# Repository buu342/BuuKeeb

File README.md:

# BuuKeeb

I've been wanting a decent mechanical keyboard for a while but I've been having a hard time finding something which fit into all of these categories:
- 100% (105 keys)
- ISO Enter
- [QMK](https://qmk.fm/) support
- LED indicators for Caps Lock, Numlock, and Scroll Lock (This one apparently is really difficult to find despite being standard in keyboards for centuries!)

I saw a Glorious PC GMMK Barebones Keyboard for 30€ which seemed to check all of these boxes (including per-key RGB which is a nice to have), but unfortunately the PCB revision I received had a crappy 8-bit MCU, which meant that writing QMK support for it would be infeasible. The case it came with was mostly metal and pretty nice however, so I decided to make a clone of the PCB, but with an STM32. This would also serve as a cool hardware design learning experience for me!

The BuuKeeb™®© features:
- 105 keys with ISO enter for the 0.01% population of the world who types on a Portuguese layout.
- Hotswappable MX switches.
- N-Key Rollover.
- Per Key LEDs on the north side, individually addressible. [OpenRGB](https://openrgb.org/) support. Key colors savable to persistent storage.
- STM32 MCU for QMK support.
- LED indicators for Caps Lock, Numlock, and Scroll Lock (incredible feature, I know).
- My face on the keyboard for added narcissism.
- Functional. Definitely.

### Keyboard Macros:

* **Alt GR + ESC** - Clear the EEPROM
* **Alt GR + F1** - Decrease the screen brightness
* **Alt GR + F2** - Increase the screen brightness
* **Alt GR + F3** - Projection mode (Windows + P)
* **Alt GR + F4** - Open search bar
* **Alt GR + F5** - Previous track
* **Alt GR + F6** - Pause/Play
* **Alt GR + F7** - Next track
* **Alt GR + F8** - Mute
* **Alt GR + F9** - Decrease volume
* **Alt GR + F10** - Increase volume
* **Alt GR + F11** - Decrease backlight brightness
* **Alt GR + F12** - Increase backlight brightness
* **Alt GR + PrntScr** - Mute microphone
* **Alt GR + ScrLck** - Eject disk
* **Alt GR + Pause** - Suspend/Sleep PC
* **CTRL + Alt GR + ESC** - Save OpenRGB Direct Mode colors to persistent memory

### Editing in KiCad

The design uses [marbastlib](https://github.com/ebastler/marbastlib) for some components so make sure you have that installed before opening the project in KiCad.

### Ordering

The `production` folder provides all the files you need for JLCPCB. You can zip up the entire folder and feed it to JLC. 

During the BOM selection, you can refer to the `bom-JLCPCB Assembly Order.xls` file to look at what components I used when I ordered my PCBs.

### Compiling the QMK Firmware:

1. Download the [OpenRGB QMK Community Module](https://gitlab.com/OpenRGBDevelopers/QMK-OpenRGB) repository.
2. Place it inside the `qmk_firmware/modules` folder and rename it to `openrgb`
3. If your copy of the qmk firmware does not ship with a `buukeeb` folder inside the `qmk_firmware/keyboards` folder, copy the QMK folder from my repository and put it inside the `qmk_firmware/keyboards`, renaming it to `buukeeb` (alternatively place a symbolic link instead).
4. Compile the firmware using your preferred method. I am on Linux so I used `qmk compile -kb buukeeb -km default`.
5. To flash the keyboard, hold down the BOOT button on the back of the board (above the 3 status indicator LEDs) and plug it into the PC. You can then let go of the button and flash it using your preferred method. I am on Linux so I used `qmk flash -kb buukeeb -km default`. 

### Special Thanks:

- [BigBass](https://github.com/bigbass1997) for helping me out with a bunch of KiCad questions and reviewing my PCB designs.
- [Keyboard Atelier Discord community](https://kbatelier.org/) for helping me and doing a keyboard review. Specific shoutouts to Quark, Indeed, Moo, The Great Advisor Xaetral™, Sune, and SenseiZéッ for answering general questions. Another big thanks to cadiremar, galile0, Jubakuba, and SenseiZéッ for the keyboard review.
- [QMK Discord community](https://discord.gg/qmk) for helping me bugfix. Specific shoutout to Drashna Jael're for identifying the LED bug.
- [OpenRGB Discord community](https://discord.gg/AQwjJPY) for answering some OpenRGB questions. Specific shoutout to CalcProgrammer1 for answering my questions.

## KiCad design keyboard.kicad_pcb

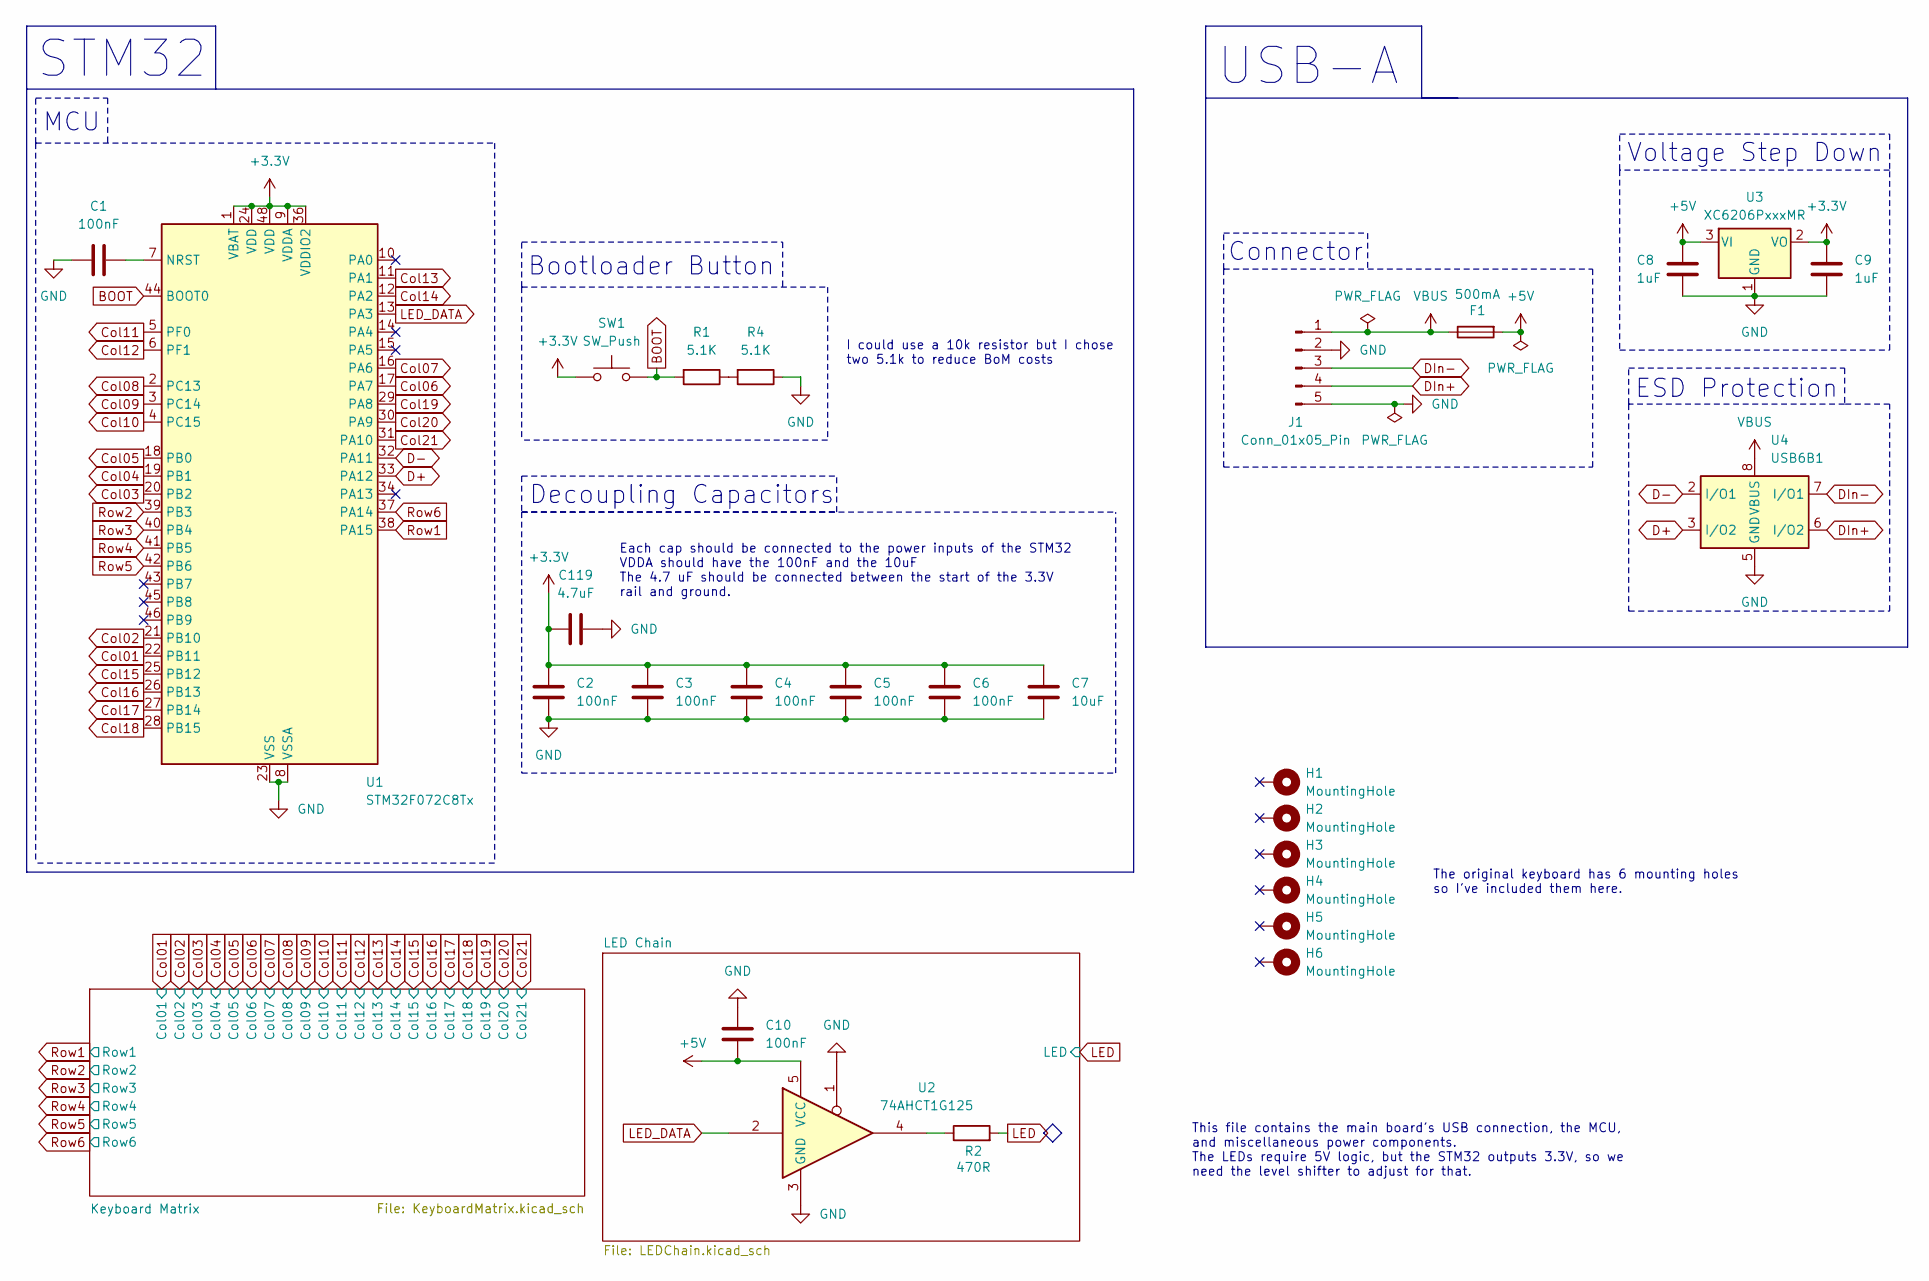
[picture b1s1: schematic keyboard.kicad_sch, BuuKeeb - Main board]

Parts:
C1, C2, C3, C4, C5, C6, C10: 100nF; C_0402_1005Metric
C7: 10uF; C_0603_1608Metric
C8, C9: 1uF; C_0603_1608Metric
C119: 4.7uF; C_0603_1608Metric
F1: 500mA; Fuse_1206_3216Metric
H1, H2, H3, H4, H5, H6: MountingHole; MountingHole_3.5mm_Pad_5.5mm
J1: Conn_01x05_Pin; PinHeader_1x05_P2.00mm_Horizontal
R1, R4: 5.1K; R_0402_1005Metric
R2: 470R; R_0402_1005Metric
SW1: SW_Push; SW_SPST_TL3342
U1: STM32F072C8Tx; LQFP-48_7x7mm_P0.5mm
U2: 74AHCT1G125; TSOP-5_1.65x3.05mm_P0.95mm
U3: XC6206PxxxMR; SOT-23-3
U4: USB6B1; SOIC-8_3.9x4.9mm_P1.27mm

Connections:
+3.3V: C2.1, C3.1, C4.1, C5.1, C6.1, C7.1, C9.1, C119.1, SW1.1, U1.1 (VBAT), U1.9 (VDDA), U1.24 (VDD), U1.36 (VDDIO2), U1.48 (VDD), U3.2 (VO)
+5V: C8.1, C10.2, F1.2, U2.5 (VCC), U3.3 (VI); also elsewhere on the board
BOOT: R1.2, SW1.2, U1.44 (BOOT0)
Col01: U1.22 (PB11); also elsewhere on the board
Col02: U1.21 (PB10); also elsewhere on the board
Col03: U1.20 (PB2); also elsewhere on the board
Col04: U1.19 (PB1); also elsewhere on the board
Col05: U1.18 (PB0); also elsewhere on the board
Col06: U1.17 (PA7); also elsewhere on the board
Col07: U1.16 (PA6); also elsewhere on the board
Col08: U1.2 (PC13); also elsewhere on the board
Col09: U1.3 (PC14); also elsewhere on the board
Col10: U1.4 (PC15); also elsewhere on the board
Col11: U1.5 (PF0); also elsewhere on the board
Col12: U1.6 (PF1); also elsewhere on the board
Col13: U1.11 (PA1); also elsewhere on the board
Col14: U1.12 (PA2); also elsewhere on the board
Col15: U1.25 (PB12); also elsewhere on the board
Col16: U1.26 (PB13); also elsewhere on the board
Col17: U1.27 (PB14); also elsewhere on the board
Col18: U1.28 (PB15); also elsewhere on the board
Col19: U1.29 (PA8); also elsewhere on the board
Col20: U1.30 (PA9); also elsewhere on the board
Col21: U1.31 (PA10); also elsewhere on the board
D+: U1.33 (PA12), U4.3 (I/O2)
D-: U1.32 (PA11), U4.2 (I/O1)
DIn+: J1.4, U4.6 (I/O2)
DIn-: J1.3, U4.7 (I/O1)
GND: C1.2, C2.2, C3.2, C4.2, C5.2, C6.2, C7.2, C8.2, C9.2, C10.1, C119.2, J1.2, J1.5, R4.1, U1.8 (VSSA), U1.23 (VSS), U1.35 (VSS), U1.47 (VSS), U2.1, U2.3 (GND), U3.1 (GND), U4.4 (GND), U4.5 (GND); also elsewhere on the board
LED: R2.2; also elsewhere on the board
LED_DATA: U1.13 (PA3), U2.2
unnamed: R1.1, R4.2
unnamed: R2.1, U2.4
unnamed: C1.1, U1.7 (NRST)
Row1: U1.38 (PA15); also elsewhere on the board
Row2: U1.39 (PB3); also elsewhere on the board
Row3: U1.40 (PB4); also elsewhere on the board
Row4: U1.41 (PB5); also elsewhere on the board
Row5: U1.42 (PB6); also elsewhere on the board
Row6: U1.37 (PA14); also elsewhere on the board
VBUS: F1.1, J1.1, U4.1 (VBUS), U4.8 (VBUS)

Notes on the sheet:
Connector
Voltage Step Down
MCU
The original keyboard has 6 mounting holes so I've included them here.
STM32
ESD Protection
Decoupling Capacitors
This file contains the main board's USB connection, the MCU, and miscellaneous power components. The LEDs require 5V logic, but the STM32 outputs 3.3V, so we need the level shifter to adjust for that.
I could use a 10k resistor but I chose two 5.1k to reduce BoM costs
USB-A
Bootloader Button
Each cap should be connected to the power inputs of the STM32 VDDA should have the 100nF and the 10uF The 4.7 uF should be connected between the start of the 3.3V rail and ground.

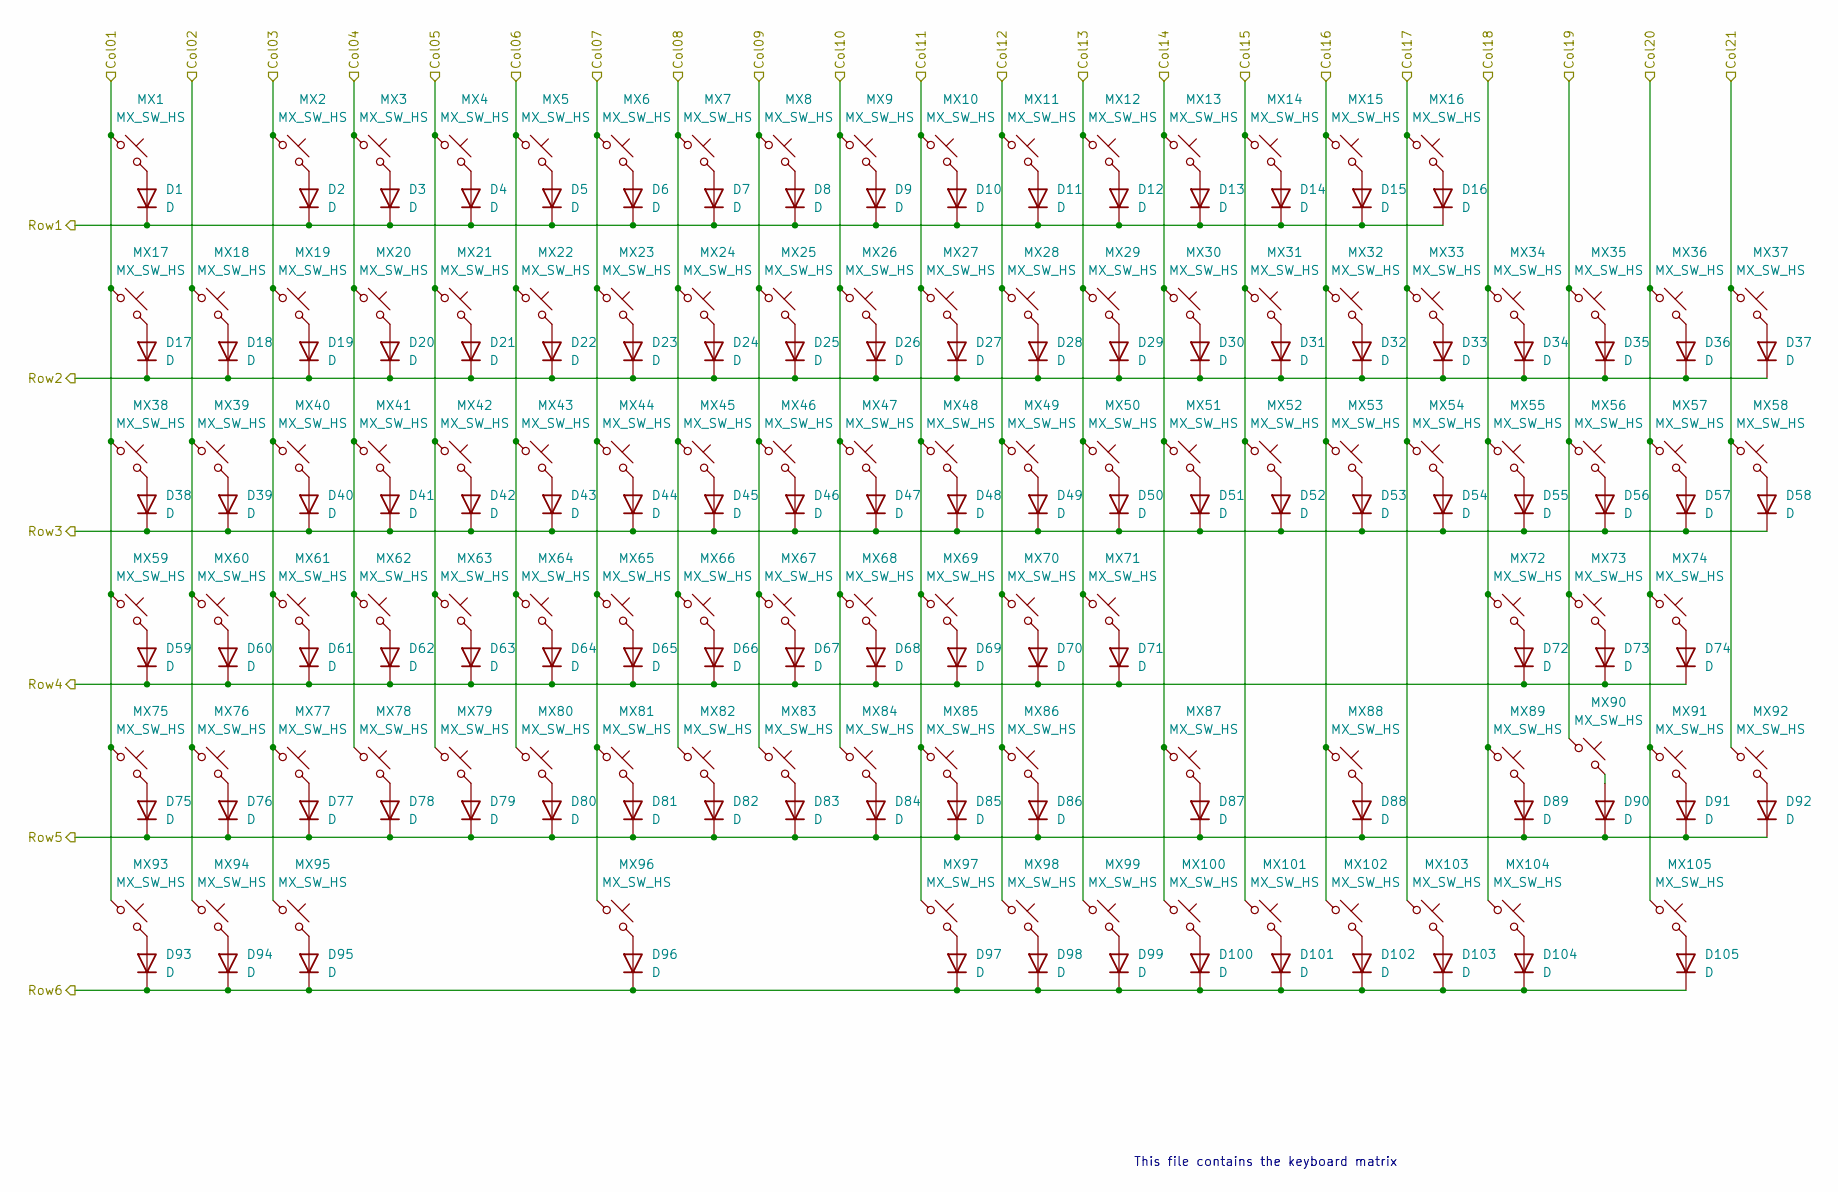
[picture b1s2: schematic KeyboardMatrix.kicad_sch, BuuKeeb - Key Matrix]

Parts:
D1, D2, D3, D4, D5, D6, D7, D8, D9, D10, D11, D12, D13, D14, D15, D16, D17, D18, D19, D20, D21, D22, D23, D24, D25, D26, D27, D28, D29, D30, D31, D32, D33, D34, D35, D36, D37, D38, D39, D40, D41, D42, D43, D44, D45, D46, D47, D48, D49, D50, D51, D52, D53, D54, D55, D56, D57, D58, D59, D60, D61, D62, D63, D64, D65, D66, D67, D68, D69, D70, D71, D72, D73, D74, D75, D76, D77, D78, D79, D80, D81, D82, D83, D84, D85, D86, D87, D88, D89, D90, D91, D92, D93, D94, D95, D96, D97, D98, D99, D100, D101, D102, D103, D104, D105: D; D_SOD-123
MX1, MX2, MX3, MX4, MX5, MX6, MX7, MX8, MX9, MX10, MX11, MX12, MX13, MX14, MX15, MX16, MX17, MX18, MX19, MX20, MX21, MX22, MX23, MX24, MX25, MX26, MX27, MX28, MX29, MX30, MX31, MX32, MX33, MX34, MX35, MX36, MX37, MX38, MX39, MX40, MX41, MX42, MX43, MX44, MX45, MX46, MX47, MX48, MX49, MX50, MX51, MX52, MX53, MX54, MX55, MX56, MX57, MX58, MX59, MX60, MX61, MX62, MX63, MX64, MX65, MX66, MX67, MX68, MX69, MX70, MX71, MX72, MX73, MX74, MX75, MX76, MX77, MX78, MX79, MX80, MX81, MX82, MX83, MX84, MX85, MX86, MX87, MX88, MX89, MX90, MX91, MX92, MX93, MX94, MX95, MX96, MX97, MX98, MX99, MX100, MX101, MX102, MX103, MX104, MX105: MX_SW_HS; SW_MX_HS_CPG151101S11_1.5u_NoHoles

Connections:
Col01: MX1.1, MX17.1, MX38.1, MX59.1, MX75.1, MX93.1; also elsewhere on the board
Col02: MX18.1, MX39.1, MX60.1, MX76.1, MX94.1; also elsewhere on the board
Col03: MX2.1, MX19.1, MX40.1, MX61.1, MX77.1, MX95.1; also elsewhere on the board
Col04: MX3.1, MX20.1, MX41.1, MX62.1, MX78.1; also elsewhere on the board
Col05: MX4.1, MX21.1, MX42.1, MX63.1, MX79.1; also elsewhere on the board
Col06: MX5.1, MX22.1, MX43.1, MX64.1, MX80.1; also elsewhere on the board
Col07: MX6.1, MX23.1, MX44.1, MX65.1, MX81.1, MX96.1; also elsewhere on the board
Col08: MX7.1, MX24.1, MX45.1, MX66.1, MX82.1; also elsewhere on the board
Col09: MX8.1, MX25.1, MX46.1, MX67.1, MX83.1; also elsewhere on the board
Col10: MX9.1, MX26.1, MX47.1, MX68.1, MX84.1; also elsewhere on the board
Col11: MX10.1, MX27.1, MX48.1, MX69.1, MX85.1, MX97.1; also elsewhere on the board
Col12: MX11.1, MX28.1, MX49.1, MX70.1, MX86.1, MX98.1; also elsewhere on the board
Col13: MX12.1, MX29.1, MX50.1, MX71.1, MX99.1; also elsewhere on the board
Col14: MX13.1, MX30.1, MX51.1, MX87.1, MX100.1; also elsewhere on the board
Col15: MX14.1, MX31.1, MX52.1, MX101.1; also elsewhere on the board
Col16: MX15.1, MX32.1, MX53.1, MX88.1, MX102.1; also elsewhere on the board
Col17: MX16.1, MX33.1, MX54.1, MX103.1; also elsewhere on the board
Col18: MX34.1, MX55.1, MX72.1, MX89.1, MX104.1; also elsewhere on the board
Col19: MX35.1, MX56.1, MX73.1, MX90.1; also elsewhere on the board
Col20: MX36.1, MX57.1, MX74.1, MX91.1, MX105.1; also elsewhere on the board
Col21: MX37.1, MX58.1, MX92.1; also elsewhere on the board
unnamed: D1.2 (A), MX1.2
unnamed: D2.2 (A), MX2.2
unnamed: D3.2 (A), MX3.2
unnamed: D4.2 (A), MX4.2
unnamed: D5.2 (A), MX5.2
unnamed: D6.2 (A), MX6.2
unnamed: D7.2 (A), MX7.2
unnamed: D8.2 (A), MX8.2
unnamed: D9.2 (A), MX9.2
unnamed: D10.2 (A), MX10.2
unnamed: D11.2 (A), MX11.2
unnamed: D12.2 (A), MX12.2
unnamed: D13.2 (A), MX13.2
unnamed: D14.2 (A), MX14.2
unnamed: D15.2 (A), MX15.2
unnamed: D16.2 (A), MX16.2
unnamed: D17.2 (A), MX17.2
unnamed: D18.2 (A), MX18.2
unnamed: D19.2 (A), MX19.2
unnamed: D20.2 (A), MX20.2
unnamed: D21.2 (A), MX21.2
unnamed: D22.2 (A), MX22.2
unnamed: D23.2 (A), MX23.2
unnamed: D24.2 (A), MX24.2
unnamed: D25.2 (A), MX25.2
unnamed: D26.2 (A), MX26.2
unnamed: D27.2 (A), MX27.2
unnamed: D28.2 (A), MX28.2
unnamed: D29.2 (A), MX29.2
unnamed: D30.2 (A), MX30.2
unnamed: D31.2 (A), MX31.2
unnamed: D32.2 (A), MX32.2
unnamed: D33.2 (A), MX33.2
unnamed: D34.2 (A), MX34.2
unnamed: D35.2 (A), MX35.2
unnamed: D36.2 (A), MX36.2
unnamed: D37.2 (A), MX37.2
unnamed: D38.2 (A), MX38.2
unnamed: D39.2 (A), MX39.2
unnamed: D40.2 (A), MX40.2
unnamed: D41.2 (A), MX41.2
unnamed: D42.2 (A), MX42.2
unnamed: D43.2 (A), MX43.2
unnamed: D44.2 (A), MX44.2
unnamed: D45.2 (A), MX45.2
unnamed: D46.2 (A), MX46.2
unnamed: D47.2 (A), MX47.2
unnamed: D48.2 (A), MX48.2
unnamed: D49.2 (A), MX49.2
unnamed: D50.2 (A), MX50.2
unnamed: D51.2 (A), MX51.2
unnamed: D52.2 (A), MX52.2
unnamed: D53.2 (A), MX53.2
unnamed: D54.2 (A), MX54.2
unnamed: D55.2 (A), MX55.2
unnamed: D56.2 (A), MX56.2
unnamed: D57.2 (A), MX57.2
unnamed: D58.2 (A), MX58.2
unnamed: D59.2 (A), MX59.2
unnamed: D60.2 (A), MX60.2
unnamed: D61.2 (A), MX61.2
unnamed: D62.2 (A), MX62.2
unnamed: D63.2 (A), MX63.2
unnamed: D64.2 (A), MX64.2
unnamed: D65.2 (A), MX65.2
unnamed: D66.2 (A), MX66.2
unnamed: D67.2 (A), MX67.2
unnamed: D68.2 (A), MX68.2
unnamed: D69.2 (A), MX69.2
unnamed: D70.2 (A), MX70.2
unnamed: D71.2 (A), MX71.2
unnamed: D72.2 (A), MX72.2
unnamed: D73.2 (A), MX73.2
unnamed: D74.2 (A), MX74.2
unnamed: D75.2 (A), MX75.2
unnamed: D76.2 (A), MX76.2
unnamed: D77.2 (A), MX77.2
unnamed: D78.2 (A), MX78.2
unnamed: D79.2 (A), MX79.2
unnamed: D80.2 (A), MX80.2
unnamed: D81.2 (A), MX81.2
unnamed: D82.2 (A), MX82.2
unnamed: D83.2 (A), MX83.2
unnamed: D84.2 (A), MX84.2
unnamed: D85.2 (A), MX85.2
unnamed: D86.2 (A), MX86.2
unnamed: D87.2 (A), MX87.2
unnamed: D88.2 (A), MX88.2
unnamed: D89.2 (A), MX89.2
unnamed: D90.2 (A), MX90.2
unnamed: D91.2 (A), MX91.2
unnamed: D92.2 (A), MX92.2
unnamed: D93.2 (A), MX93.2
unnamed: D94.2 (A), MX94.2
unnamed: D95.2 (A), MX95.2
unnamed: D96.2 (A), MX96.2
unnamed: D97.2 (A), MX97.2
unnamed: D98.2 (A), MX98.2
unnamed: D99.2 (A), MX99.2
unnamed: D100.2 (A), MX100.2
unnamed: D101.2 (A), MX101.2
unnamed: D102.2 (A), MX102.2
unnamed: D103.2 (A), MX103.2
unnamed: D104.2 (A), MX104.2
unnamed: D105.2 (A), MX105.2
Row1: D1.1 (K), D2.1 (K), D3.1 (K), D4.1 (K), D5.1 (K), D6.1 (K), D7.1 (K), D8.1 (K), D9.1 (K), D10.1 (K), D11.1 (K), D12.1 (K), D13.1 (K), D14.1 (K), D15.1 (K), D16.1 (K); also elsewhere on the board
Row2: D17.1 (K), D18.1 (K), D19.1 (K), D20.1 (K), D21.1 (K), D22.1 (K), D23.1 (K), D24.1 (K), D25.1 (K), D26.1 (K), D27.1 (K), D28.1 (K), D29.1 (K), D30.1 (K), D31.1 (K), D32.1 (K), D33.1 (K), D34.1 (K), D35.1 (K), D36.1 (K), D37.1 (K); also elsewhere on the board
Row3: D38.1 (K), D39.1 (K), D40.1 (K), D41.1 (K), D42.1 (K), D43.1 (K), D44.1 (K), D45.1 (K), D46.1 (K), D47.1 (K), D48.1 (K), D49.1 (K), D50.1 (K), D51.1 (K), D52.1 (K), D53.1 (K), D54.1 (K), D55.1 (K), D56.1 (K), D57.1 (K), D58.1 (K); also elsewhere on the board
Row4: D59.1 (K), D60.1 (K), D61.1 (K), D62.1 (K), D63.1 (K), D64.1 (K), D65.1 (K), D66.1 (K), D67.1 (K), D68.1 (K), D69.1 (K), D70.1 (K), D71.1 (K), D72.1 (K), D73.1 (K), D74.1 (K); also elsewhere on the board
Row5: D75.1 (K), D76.1 (K), D77.1 (K), D78.1 (K), D79.1 (K), D80.1 (K), D81.1 (K), D82.1 (K), D83.1 (K), D84.1 (K), D85.1 (K), D86.1 (K), D87.1 (K), D88.1 (K), D89.1 (K), D90.1 (K), D91.1 (K), D92.1 (K); also elsewhere on the board
Row6: D93.1 (K), D94.1 (K), D95.1 (K), D96.1 (K), D97.1 (K), D98.1 (K), D99.1 (K), D100.1 (K), D101.1 (K), D102.1 (K), D103.1 (K), D104.1 (K), D105.1 (K); also elsewhere on the board

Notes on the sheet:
This file contains the keyboard matrix

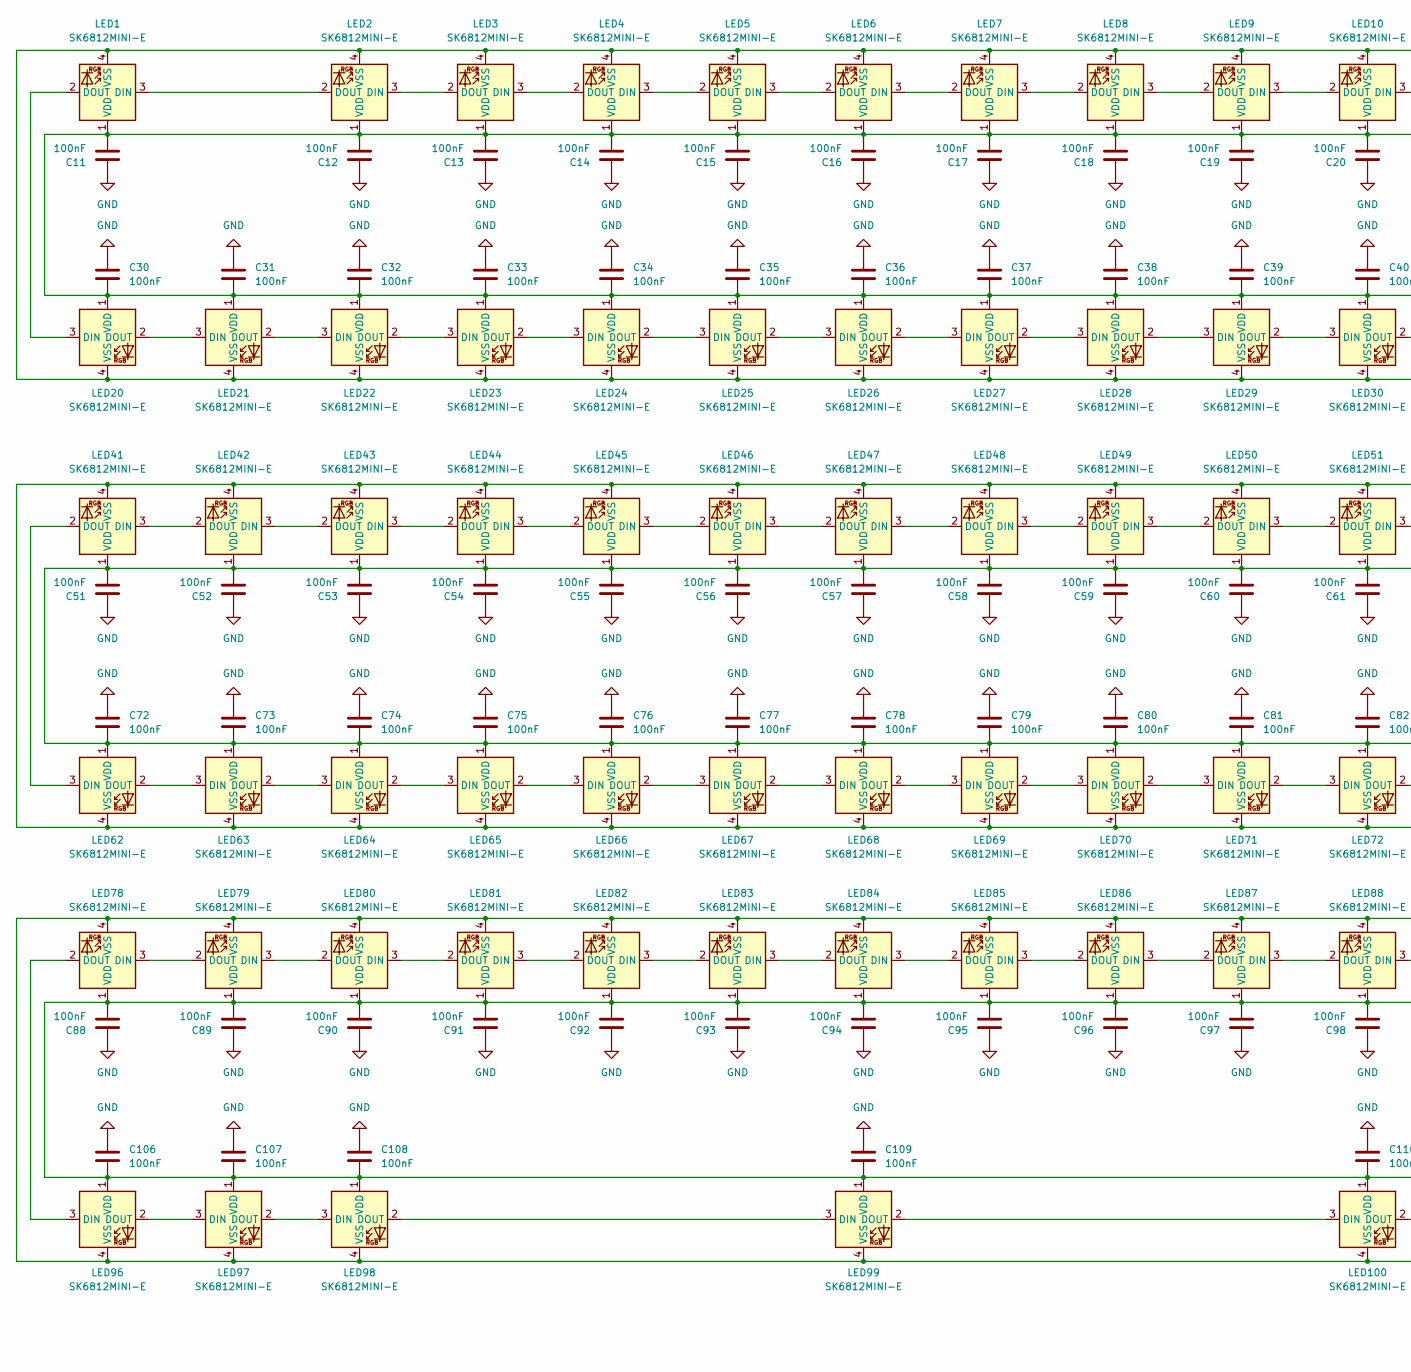
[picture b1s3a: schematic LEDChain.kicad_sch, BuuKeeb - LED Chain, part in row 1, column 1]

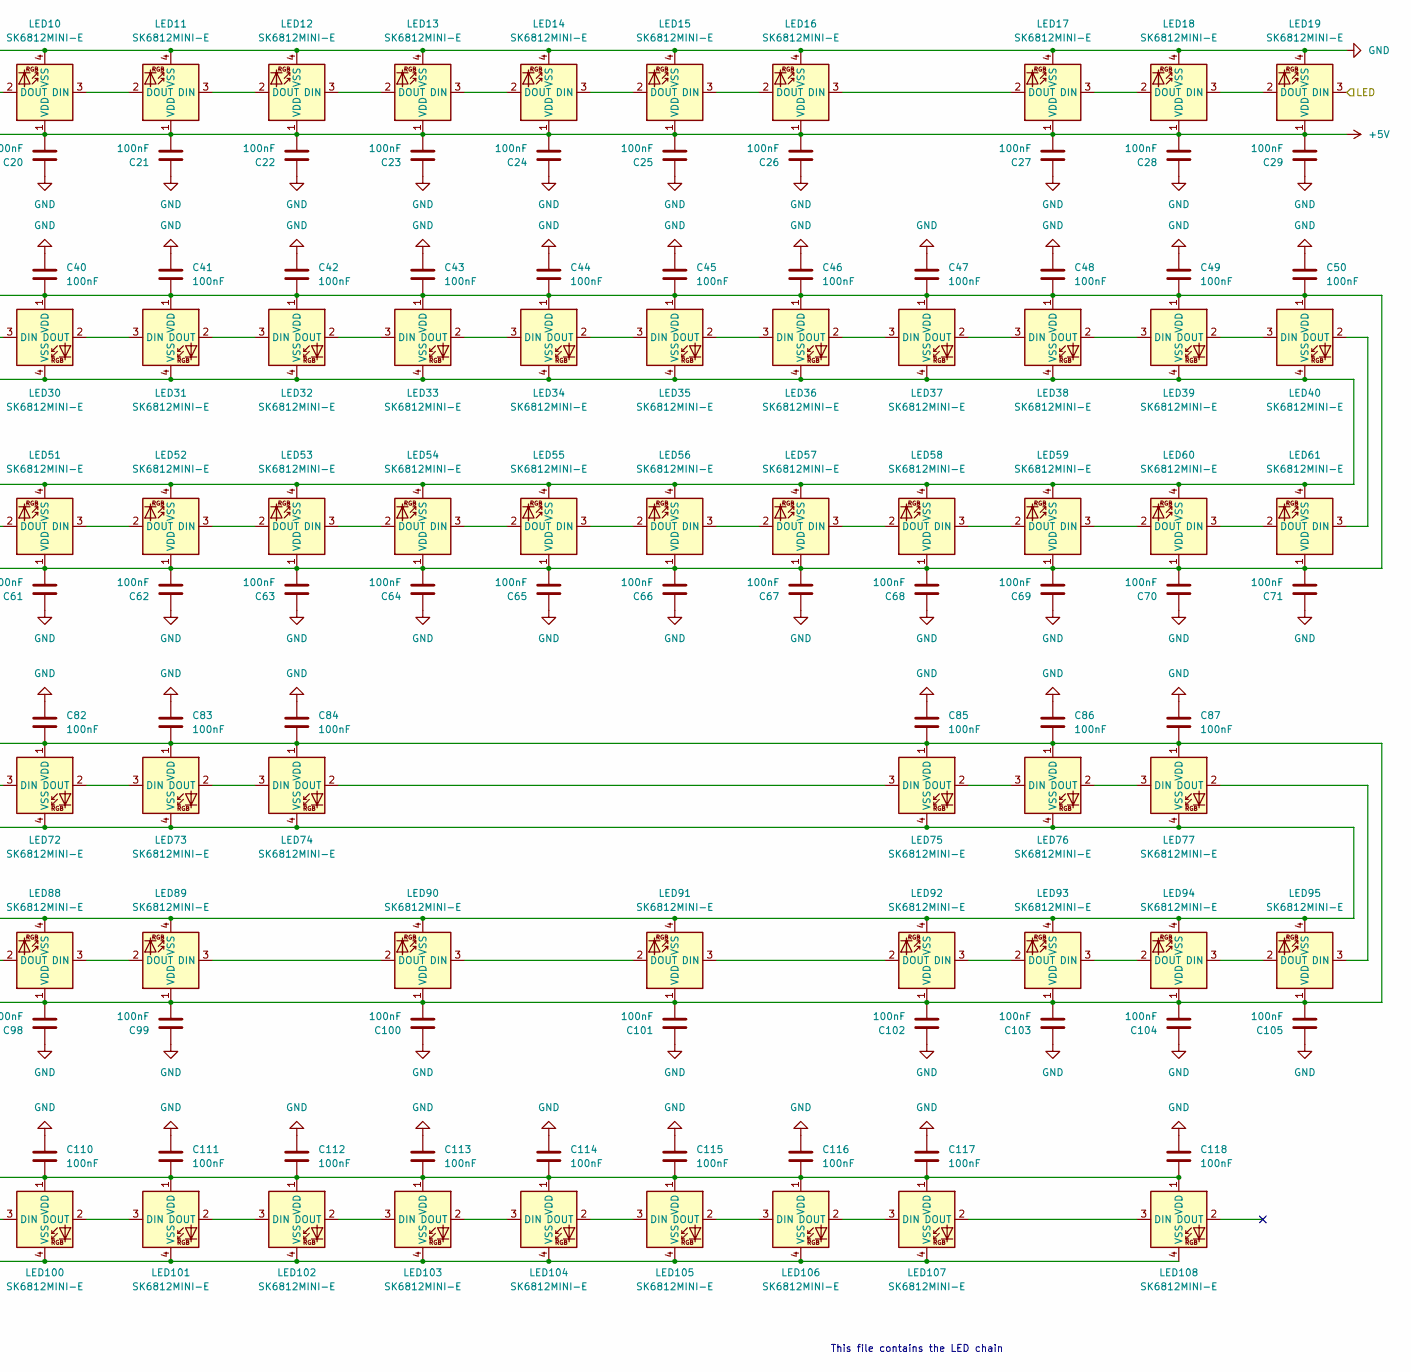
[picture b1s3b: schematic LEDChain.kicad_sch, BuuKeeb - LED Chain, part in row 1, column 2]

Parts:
C11, C12, C13, C14, C15, C16, C17, C18, C19, C20, C21, C22, C23, C24, C25, C26, C27, C28, C29, C30, C31, C32, C33, C34, C35, C36, C37, C38, C39, C40, C41, C42, C43, C44, C45, C46, C47, C48, C49, C50, C51, C52, C53, C54, C55, C56, C57, C58, C59, C60, C61, C62, C63, C64, C65, C66, C67, C68, C69, C70, C71, C72, C73, C74, C75, C76, C77, C78, C79, C80, C81, C82, C83, C84, C85, C86, C87, C88, C89, C90, C91, C92, C93, C94, C95, C96, C97, C98, C99, C100, C101, C102, C103, C104, C105, C106, C107, C108, C109, C110, C111, C112, C113, C114, C115, C116, C117, C118: 100nF; C_0402_1005Metric
LED1, LED2, LED3, LED4, LED5, LED6, LED7, LED8, LED9, LED10, LED11, LED12, LED13, LED14, LED15, LED16, LED17, LED18, LED19, LED20, LED21, LED22, LED23, LED24, LED25, LED26, LED27, LED28, LED29, LED30, LED31, LED32, LED33, LED34, LED35, LED36, LED37, LED38, LED39, LED40, LED41, LED42, LED43, LED44, LED45, LED46, LED47, LED48, LED49, LED50, LED51, LED52, LED53, LED54, LED55, LED56, LED57, LED58, LED59, LED60, LED61, LED62, LED63, LED64, LED65, LED66, LED67, LED68, LED69, LED70, LED71, LED72, LED73, LED74, LED75, LED76, LED77, LED78, LED79, LED80, LED81, LED82, LED83, LED84, LED85, LED86, LED87, LED88, LED89, LED90, LED91, LED92, LED93, LED94, LED95, LED96, LED97, LED98, LED99, LED100, LED101, LED102, LED103, LED104, LED105, LED106, LED107, LED108: SK6812MINI-E; LED_6028R_NoHoles

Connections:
+5V: C11.2, C12.2, C13.2, C14.2, C15.2, C16.2, C17.2, C18.2, C19.2, C20.2, C21.2, C22.2, C23.2, C24.2, C25.2, C26.2, C27.2, C28.2, C29.1, C30.2, C31.2, C32.2, C33.2, C34.2, C35.2, C36.2, C37.2, C38.2, C39.2, C40.2, C41.2, C42.2, C43.2, C44.2, C45.2, C46.2, C47.2, C48.2, C49.2, C50.2, C51.2, C52.2, C53.2, C54.2, C55.2, C56.2, C57.2, C58.2, C59.2, C60.2, C61.2, C62.2, C63.2, C64.2, C65.2, C66.2, C67.2, C68.2, C69.2, C70.2, C71.2, C72.2, C73.2, C74.2, C75.2, C76.2, C77.2, C78.2, C79.2, C80.2, C81.2, C82.2, C83.2, C84.2, C85.2, C86.2, C87.2, C88.2, C89.2, C90.2, C91.2, C92.2, C93.2, C94.2, C95.2, C96.2, C97.2, C98.2, C99.2, C100.2, C101.2, C102.2, C103.2, C104.2, C105.2, C106.2, C107.2, C108.2, C109.2, C110.2, C111.2, C112.2, C113.2, C114.2, C115.2, C116.2, C117.2, C118.2, LED1.1 (VDD), LED2.1 (VDD), LED3.1 (VDD), LED4.1 (VDD), LED5.1 (VDD), LED6.1 (VDD), LED7.1 (VDD), LED8.1 (VDD), LED9.1 (VDD), LED10.1 (VDD), LED11.1 (VDD), LED12.1 (VDD), LED13.1 (VDD), LED14.1 (VDD), LED15.1 (VDD), LED16.1 (VDD), LED17.1 (VDD), LED18.1 (VDD), LED19.1 (VDD), LED20.1 (VDD), LED21.1 (VDD), LED22.1 (VDD), LED23.1 (VDD), LED24.1 (VDD), LED25.1 (VDD), LED26.1 (VDD), LED27.1 (VDD), LED28.1 (VDD), LED29.1 (VDD), LED30.1 (VDD), LED31.1 (VDD), LED32.1 (VDD), LED33.1 (VDD), LED34.1 (VDD), LED35.1 (VDD), LED36.1 (VDD), LED37.1 (VDD), LED38.1 (VDD), LED39.1 (VDD), LED40.1 (VDD), LED41.1 (VDD), LED42.1 (VDD), LED43.1 (VDD), LED44.1 (VDD), LED45.1 (VDD), LED46.1 (VDD), LED47.1 (VDD), LED48.1 (VDD), LED49.1 (VDD), LED50.1 (VDD), LED51.1 (VDD), LED52.1 (VDD), LED53.1 (VDD), LED54.1 (VDD), LED55.1 (VDD), LED56.1 (VDD), LED57.1 (VDD), LED58.1 (VDD), LED59.1 (VDD), LED60.1 (VDD), LED61.1 (VDD), LED62.1 (VDD), LED63.1 (VDD), LED64.1 (VDD), LED65.1 (VDD), LED66.1 (VDD), LED67.1 (VDD), LED68.1 (VDD), LED69.1 (VDD), LED70.1 (VDD), LED71.1 (VDD), LED72.1 (VDD), LED73.1 (VDD), LED74.1 (VDD), LED75.1 (VDD), LED76.1 (VDD), LED77.1 (VDD), LED78.1 (VDD), LED79.1 (VDD), LED80.1 (VDD), LED81.1 (VDD), LED82.1 (VDD), LED83.1 (VDD), LED84.1 (VDD), LED85.1 (VDD), LED86.1 (VDD), LED87.1 (VDD), LED88.1 (VDD), LED89.1 (VDD), LED90.1 (VDD), LED91.1 (VDD), LED92.1 (VDD), LED93.1 (VDD), LED94.1 (VDD), LED95.1 (VDD), LED96.1 (VDD), LED97.1 (VDD), LED98.1 (VDD), LED99.1 (VDD), LED100.1 (VDD), LED101.1 (VDD), LED102.1 (VDD), LED103.1 (VDD), LED104.1 (VDD), LED105.1 (VDD), LED106.1 (VDD), LED107.1 (VDD), LED108.1 (VDD); also elsewhere on the board
GND: C11.1, C12.1, C13.1, C14.1, C15.1, C16.1, C17.1, C18.1, C19.1, C20.1, C21.1, C22.1, C23.1, C24.1, C25.1, C26.1, C27.1, C28.1, C29.2, C30.1, C31.1, C32.1, C33.1, C34.1, C35.1, C36.1, C37.1, C38.1, C39.1, C40.1, C41.1, C42.1, C43.1, C44.1, C45.1, C46.1, C47.1, C48.1, C49.1, C50.1, C51.1, C52.1, C53.1, C54.1, C55.1, C56.1, C57.1, C58.1, C59.1, C60.1, C61.1, C62.1, C63.1, C64.1, C65.1, C66.1, C67.1, C68.1, C69.1, C70.1, C71.1, C72.1, C73.1, C74.1, C75.1, C76.1, C77.1, C78.1, C79.1, C80.1, C81.1, C82.1, C83.1, C84.1, C85.1, C86.1, C87.1, C88.1, C89.1, C90.1, C91.1, C92.1, C93.1, C94.1, C95.1, C96.1, C97.1, C98.1, C99.1, C100.1, C101.1, C102.1, C103.1, C104.1, C105.1, C106.1, C107.1, C108.1, C109.1, C110.1, C111.1, C112.1, C113.1, C114.1, C115.1, C116.1, C117.1, C118.1, LED1.4 (VSS), LED2.4 (VSS), LED3.4 (VSS), LED4.4 (VSS), LED5.4 (VSS), LED6.4 (VSS), LED7.4 (VSS), LED8.4 (VSS), LED9.4 (VSS), LED10.4 (VSS), LED11.4 (VSS), LED12.4 (VSS), LED13.4 (VSS), LED14.4 (VSS), LED15.4 (VSS), LED16.4 (VSS), LED17.4 (VSS), LED18.4 (VSS), LED19.4 (VSS), LED20.4 (VSS), LED21.4 (VSS), LED22.4 (VSS), LED23.4 (VSS), LED24.4 (VSS), LED25.4 (VSS), LED26.4 (VSS), LED27.4 (VSS), LED28.4 (VSS), LED29.4 (VSS), LED30.4 (VSS), LED31.4 (VSS), LED32.4 (VSS), LED33.4 (VSS), LED34.4 (VSS), LED35.4 (VSS), LED36.4 (VSS), LED37.4 (VSS), LED38.4 (VSS), LED39.4 (VSS), LED40.4 (VSS), LED41.4 (VSS), LED42.4 (VSS), LED43.4 (VSS), LED44.4 (VSS), LED45.4 (VSS), LED46.4 (VSS), LED47.4 (VSS), LED48.4 (VSS), LED49.4 (VSS), LED50.4 (VSS), LED51.4 (VSS), LED52.4 (VSS), LED53.4 (VSS), LED54.4 (VSS), LED55.4 (VSS), LED56.4 (VSS), LED57.4 (VSS), LED58.4 (VSS), LED59.4 (VSS), LED60.4 (VSS), LED61.4 (VSS), LED62.4 (VSS), LED63.4 (VSS), LED64.4 (VSS), LED65.4 (VSS), LED66.4 (VSS), LED67.4 (VSS), LED68.4 (VSS), LED69.4 (VSS), LED70.4 (VSS), LED71.4 (VSS), LED72.4 (VSS), LED73.4 (VSS), LED74.4 (VSS), LED75.4 (VSS), LED76.4 (VSS), LED77.4 (VSS), LED78.4 (VSS), LED79.4 (VSS), LED80.4 (VSS), LED81.4 (VSS), LED82.4 (VSS), LED83.4 (VSS), LED84.4 (VSS), LED85.4 (VSS), LED86.4 (VSS), LED87.4 (VSS), LED88.4 (VSS), LED89.4 (VSS), LED90.4 (VSS), LED91.4 (VSS), LED92.4 (VSS), LED93.4 (VSS), LED94.4 (VSS), LED95.4 (VSS), LED96.4 (VSS), LED97.4 (VSS), LED98.4 (VSS), LED99.4 (VSS), LED100.4 (VSS), LED101.4 (VSS), LED102.4 (VSS), LED103.4 (VSS), LED104.4 (VSS), LED105.4 (VSS), LED106.4 (VSS), LED107.4 (VSS), LED108.4 (VSS); also elsewhere on the board
LED: LED19.3 (DIN); also elsewhere on the board
unnamed: LED1.3 (DIN), LED2.2 (DOUT)
unnamed: LED1.2 (DOUT), LED20.3 (DIN)
unnamed: LED2.3 (DIN), LED3.2 (DOUT)
unnamed: LED3.3 (DIN), LED4.2 (DOUT)
unnamed: LED4.3 (DIN), LED5.2 (DOUT)
unnamed: LED5.3 (DIN), LED6.2 (DOUT)
unnamed: LED6.3 (DIN), LED7.2 (DOUT)
unnamed: LED7.3 (DIN), LED8.2 (DOUT)
unnamed: LED8.3 (DIN), LED9.2 (DOUT)
unnamed: LED10.3 (DIN), LED11.2 (DOUT)
unnamed: LED9.3 (DIN), LED10.2 (DOUT)
unnamed: LED11.3 (DIN), LED12.2 (DOUT)
unnamed: LED12.3 (DIN), LED13.2 (DOUT)
unnamed: LED13.3 (DIN), LED14.2 (DOUT)
unnamed: LED14.3 (DIN), LED15.2 (DOUT)
unnamed: LED15.3 (DIN), LED16.2 (DOUT)
unnamed: LED16.3 (DIN), LED17.2 (DOUT)
unnamed: LED17.3 (DIN), LED18.2 (DOUT)
unnamed: LED18.3 (DIN), LED19.2 (DOUT)
unnamed: LED20.2 (DOUT), LED21.3 (DIN)
unnamed: LED21.2 (DOUT), LED22.3 (DIN)
unnamed: LED22.2 (DOUT), LED23.3 (DIN)
unnamed: LED23.2 (DOUT), LED24.3 (DIN)
unnamed: LED24.2 (DOUT), LED25.3 (DIN)
unnamed: LED25.2 (DOUT), LED26.3 (DIN)
unnamed: LED26.2 (DOUT), LED27.3 (DIN)
unnamed: LED27.2 (DOUT), LED28.3 (DIN)
unnamed: LED28.2 (DOUT), LED29.3 (DIN)
unnamed: LED29.2 (DOUT), LED30.3 (DIN)
unnamed: LED30.2 (DOUT), LED31.3 (DIN)
unnamed: LED31.2 (DOUT), LED32.3 (DIN)
unnamed: LED32.2 (DOUT), LED33.3 (DIN)
unnamed: LED33.2 (DOUT), LED34.3 (DIN)
unnamed: LED34.2 (DOUT), LED35.3 (DIN)
unnamed: LED35.2 (DOUT), LED36.3 (DIN)
unnamed: LED36.2 (DOUT), LED37.3 (DIN)
unnamed: LED37.2 (DOUT), LED38.3 (DIN)
unnamed: LED38.2 (DOUT), LED39.3 (DIN)
unnamed: LED39.2 (DOUT), LED40.3 (DIN)
unnamed: LED40.2 (DOUT), LED61.3 (DIN)
unnamed: LED41.3 (DIN), LED42.2 (DOUT)
unnamed: LED41.2 (DOUT), LED62.3 (DIN)
unnamed: LED42.3 (DIN), LED43.2 (DOUT)
unnamed: LED43.3 (DIN), LED44.2 (DOUT)
unnamed: LED44.3 (DIN), LED45.2 (DOUT)
unnamed: LED45.3 (DIN), LED46.2 (DOUT)
unnamed: LED46.3 (DIN), LED47.2 (DOUT)
unnamed: LED47.3 (DIN), LED48.2 (DOUT)
unnamed: LED48.3 (DIN), LED49.2 (DOUT)
unnamed: LED49.3 (DIN), LED50.2 (DOUT)
unnamed: LED50.3 (DIN), LED51.2 (DOUT)
unnamed: LED51.3 (DIN), LED52.2 (DOUT)
unnamed: LED52.3 (DIN), LED53.2 (DOUT)
unnamed: LED53.3 (DIN), LED54.2 (DOUT)
unnamed: LED54.3 (DIN), LED55.2 (DOUT)
unnamed: LED55.3 (DIN), LED56.2 (DOUT)
unnamed: LED56.3 (DIN), LED57.2 (DOUT)
unnamed: LED57.3 (DIN), LED58.2 (DOUT)
unnamed: LED58.3 (DIN), LED59.2 (DOUT)
unnamed: LED59.3 (DIN), LED60.2 (DOUT)
unnamed: LED60.3 (DIN), LED61.2 (DOUT)
unnamed: LED62.2 (DOUT), LED63.3 (DIN)
unnamed: LED63.2 (DOUT), LED64.3 (DIN)
unnamed: LED64.2 (DOUT), LED65.3 (DIN)
unnamed: LED65.2 (DOUT), LED66.3 (DIN)
unnamed: LED66.2 (DOUT), LED67.3 (DIN)
unnamed: LED67.2 (DOUT), LED68.3 (DIN)
unnamed: LED68.2 (DOUT), LED69.3 (DIN)
unnamed: LED69.2 (DOUT), LED70.3 (DIN)
unnamed: LED70.2 (DOUT), LED71.3 (DIN)
unnamed: LED71.2 (DOUT), LED72.3 (DIN)
unnamed: LED72.2 (DOUT), LED73.3 (DIN)
unnamed: LED73.2 (DOUT), LED74.3 (DIN)
unnamed: LED74.2 (DOUT), LED75.3 (DIN)
unnamed: LED75.2 (DOUT), LED76.3 (DIN)
unnamed: LED76.2 (DOUT), LED77.3 (DIN)
unnamed: LED77.2 (DOUT), LED95.3 (DIN)
unnamed: LED78.3 (DIN), LED79.2 (DOUT)
unnamed: LED78.2 (DOUT), LED96.3 (DIN)
unnamed: LED79.3 (DIN), LED80.2 (DOUT)
unnamed: LED80.3 (DIN), LED81.2 (DOUT)
unnamed: LED81.3 (DIN), LED82.2 (DOUT)
unnamed: LED82.3 (DIN), LED83.2 (DOUT)
unnamed: LED83.3 (DIN), LED84.2 (DOUT)
unnamed: LED84.3 (DIN), LED85.2 (DOUT)
unnamed: LED85.3 (DIN), LED86.2 (DOUT)
unnamed: LED86.3 (DIN), LED87.2 (DOUT)
unnamed: LED87.3 (DIN), LED88.2 (DOUT)
unnamed: LED88.3 (DIN), LED89.2 (DOUT)
unnamed: LED89.3 (DIN), LED90.2 (DOUT)
unnamed: LED90.3 (DIN), LED91.2 (DOUT)
unnamed: LED91.3 (DIN), LED92.2 (DOUT)
unnamed: LED92.3 (DIN), LED93.2 (DOUT)
unnamed: LED93.3 (DIN), LED94.2 (DOUT)
unnamed: LED94.3 (DIN), LED95.2 (DOUT)
unnamed: LED96.2 (DOUT), LED97.3 (DIN)
unnamed: LED97.2 (DOUT), LED98.3 (DIN)
unnamed: LED98.2 (DOUT), LED99.3 (DIN)
unnamed: LED99.2 (DOUT), LED100.3 (DIN)
unnamed: LED100.2 (DOUT), LED101.3 (DIN)
unnamed: LED101.2 (DOUT), LED102.3 (DIN)
unnamed: LED102.2 (DOUT), LED103.3 (DIN)
unnamed: LED103.2 (DOUT), LED104.3 (DIN)
unnamed: LED104.2 (DOUT), LED105.3 (DIN)
unnamed: LED105.2 (DOUT), LED106.3 (DIN)
unnamed: LED106.2 (DOUT), LED107.3 (DIN)
unnamed: LED107.2 (DOUT), LED108.3 (DIN)

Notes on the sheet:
This file contains the LED chain

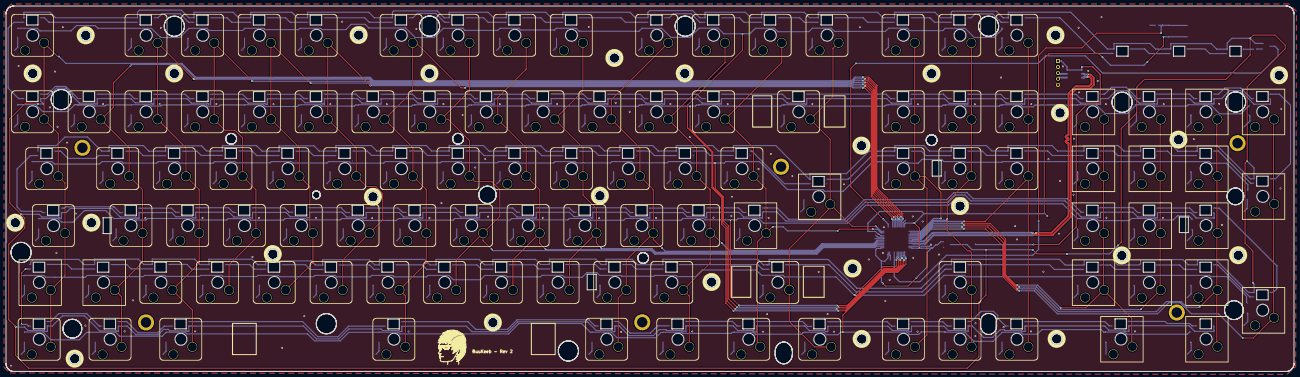
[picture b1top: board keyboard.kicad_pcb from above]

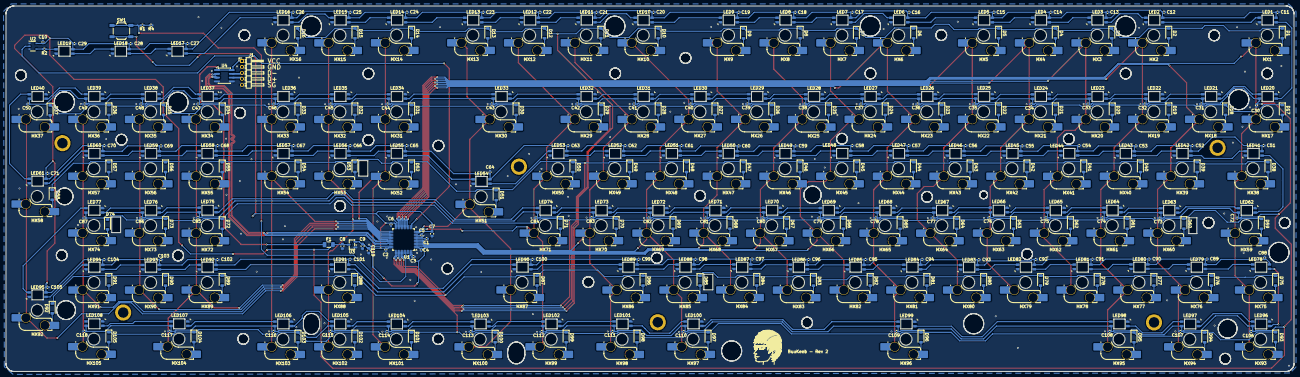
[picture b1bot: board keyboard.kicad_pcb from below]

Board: 2 copper layers, 431.0 x 122.3 mm, 453 parts (447 on the bottom side), 253 nets.

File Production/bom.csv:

Designator,Footprint,Quantity,Value,LCSC Part #
"C1, C10, C100, C101, C102, C103, C104, C105, C106, C107, C108, C109, C11, C110, C111, C112, C113, C114, C115, C116, C117, C118, C12, C13, C14, C15, C16, C17, C18, C19, C2, C20, C21, C22, C23, C24, C25, C26, C27, C28, C29, C3, C30, C31, C32, C33, C34, C35, C36, C37, C38, C39, C4, C40, C41, C42, C43, C44, C45, C46, C47, C48, C49, C5, C50, C51, C52, C53, C54, C55, C56, C57, C58, C59, C6, C60, C61, C62, C63, C64, C65, C66, C67, C68, C69, C70, C71, C72, C73, C74, C75, C76, C77, C78, C79, C80, C81, C82, C83, C84, C85, C86, C87, C88, C89, C90, C91, C92, C93, C94, C95, C96, C97, C98, C99",0402,115,100nF,
C119,0603,1,4.7uF,
C7,0603,1,10uF,
"C8, C9",0603,2,1uF,
"D1, D10, D100, D101, D102, D103, D104, D105, D11, D12, D13, D14, D15, D16, D17, D18, D19, D2, D20, D21, D22, D23, D24, D25, D26, D27, D28, D29, D3, D30, D31, D32, D33, D34, D35, D36, D37, D38, D39, D4, D40, D41, D42, D43, D44, D45, D46, D47, D48, D49, D5, D50, D51, D52, D53, D54, D55, D56, D57, D58, D59, D6, D60, D61, D62, D63, D64, D65, D66, D67, D68, D69, D7, D70, D71, D72, D73, D74, D75, D76, D77, D78, D79, D8, D80, D81, D82, D83, D84, D85, D86, D87, D88, D89, D9, D90, D91, D92, D93, D94, D95, D96, D97, D98, D99",D_SOD-123,105,D,
F1,1206,1,500mA,
J1,PinHeader_1x05_P2.00mm_Horizontal,1,Conn_01x05_Pin,
"LED1, LED10, LED100, LED101, LED102, LED103, LED104, LED105, LED106, LED107, LED108, LED11, LED12, LED13, LED14, LED15, LED16, LED17, LED18, LED19, LED2, LED20, LED21, LED22, LED23, LED24, LED25, LED26, LED27, LED28, LED29, LED3, LED30, LED31, LED32, LED33, LED34, LED35, LED36, LED37, LED38, LED39, LED4, LED40, LED41, LED42, LED43, LED44, LED45, LED46, LED47, LED48, LED49, LED5, LED50, LED51, LED52, LED53, LED54, LED55, LED56, LED57, LED58, LED59, LED6, LED60, LED61, LED62, LED63, LED64, LED65, LED66, LED67, LED68, LED69, LED7, LED70, LED71, LED72, LED73, LED74, LED75, LED76, LED77, LED78, LED79, LED8, LED80, LED81, LED82, LED83, LED84, LED85, LED86, LED87, LED88, LED89, LED9, LED90, LED91, LED92, LED93, LED94, LED95, LED96, LED97, LED98, LED99",LED_6028R_NoHoles,108,SK6812MINI-E,
"MX1, MX10, MX100, MX101, MX102, MX103, MX104, MX105, MX11, MX12, MX13, MX14, MX15, MX16, MX17, MX18, MX19, MX2, MX20, MX21, MX22, MX23, MX24, MX25, MX26, MX27, MX28, MX29, MX3, MX30, MX31, MX32, MX33, MX34, MX35, MX36, MX37, MX38, MX39, MX4, MX40, MX41, MX42, MX43, MX44, MX45, MX46, MX47, MX48, MX49, MX5, MX50, MX51, MX52, MX53, MX54, MX55, MX56, MX57, MX58, MX59, MX6, MX60, MX61, MX62, MX63, MX64, MX65, MX66, MX67, MX68, MX69, MX7, MX70, MX71, MX72, MX73, MX74, MX75, MX76, MX77, MX78, MX79, MX8, MX80, MX81, MX82, MX83, MX84, MX85, MX86, MX87, MX88, MX89, MX9, MX90, MX91, MX92, MX93, MX94, MX95, MX96, MX97, MX98, MX99",SW_MX_HS_CPG151101S11_1.5u_NoHoles,105,MX_SW_HS,
"R1, R4",0402,2,5.1K,
R2,0402,1,470R,
SW1,SW_SPST_TL3342,1,SW_Push,
U1,LQFP-48_7x7mm_P0.5mm,1,STM32F072C8Tx,
U2,TSOP-5_1.65x3.05mm_P0.95mm,1,74AHCT1G125,
U3,SOT-23-3,1,XC6206PxxxMR,
U4,SOIC-8_3.9x4.9mm_P1.27mm,1,USB6B1,
